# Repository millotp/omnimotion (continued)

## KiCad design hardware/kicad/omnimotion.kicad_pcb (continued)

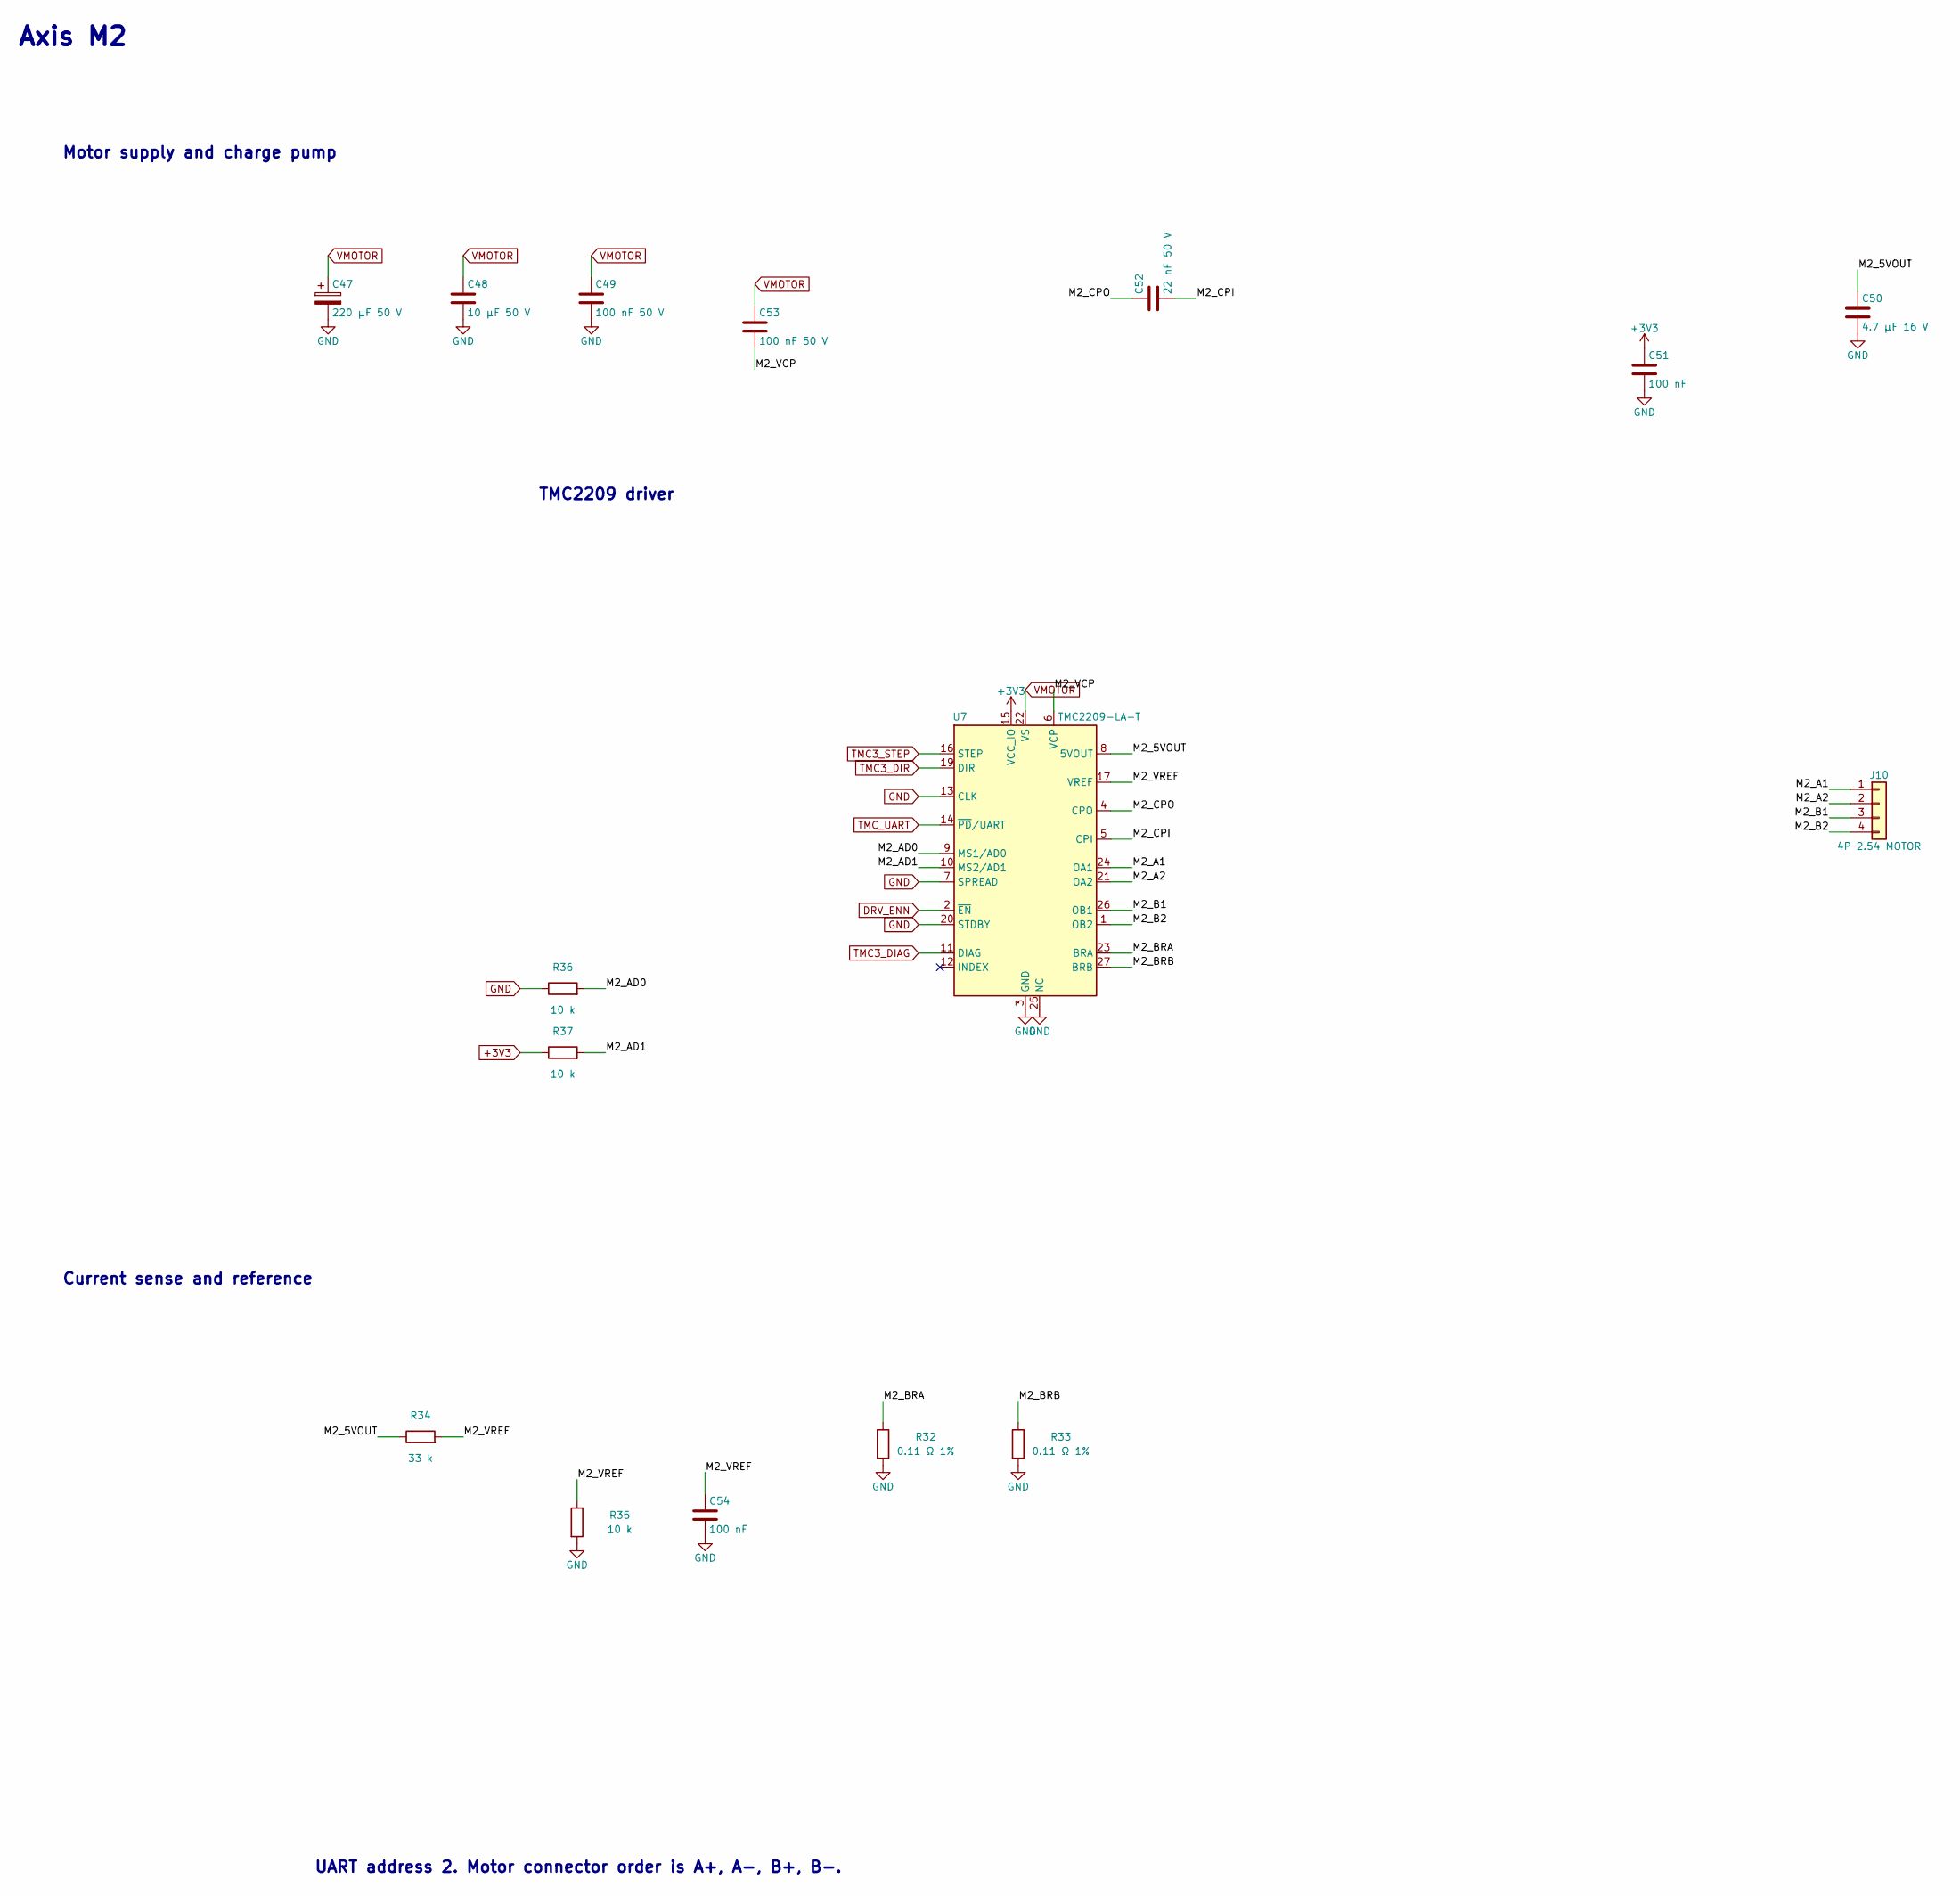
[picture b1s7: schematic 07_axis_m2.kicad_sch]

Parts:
C47: 220 µF 50 V; CP_Elec_10x10.5
C48: 10 µF 50 V; C_1210_3225Metric
C49, C53: 100 nF 50 V; C_0603_1608Metric
C50: 4.7 µF 16 V; C_0603_1608Metric
C51, C54: 100 nF; C_0603_1608Metric
C52: 22 nF 50 V; C_0603_1608Metric
J10: 4P 2.54 MOTOR; PinHeader_1x04_P2.54mm_Vertical
R32, R33: 0.11 Ω 1%; R_2512_6332Metric
R34: 33 k; R_0603_1608Metric
R35, R36, R37: 10 k; R_0603_1608Metric
U7: TMC2209-LA-T; TMC2209_VQFN28_ThermalVias_0.3mm

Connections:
+3V3: C51.1, R37.1, U7.15 (VCC_IO); also elsewhere on the board
/Axis M2 - UART address 2/M2_5VOUT: C50.1, R34.1, U7.8 (5VOUT)
/Axis M2 - UART address 2/M2_A1: J10.1, U7.24 (OA1)
/Axis M2 - UART address 2/M2_A2: J10.2, U7.21 (OA2)
/Axis M2 - UART address 2/M2_AD0: R36.2, U7.9 (MS1/AD0)
/Axis M2 - UART address 2/M2_AD1: R37.2, U7.10 (MS2/AD1)
/Axis M2 - UART address 2/M2_B1: J10.3, U7.26 (OB1)
/Axis M2 - UART address 2/M2_B2: J10.4, U7.1 (OB2)
/Axis M2 - UART address 2/M2_BRA: R32.1, U7.23 (BRA)
/Axis M2 - UART address 2/M2_BRB: R33.1, U7.27 (BRB)
/Axis M2 - UART address 2/M2_CPI: C52.2, U7.5 (CPI)
/Axis M2 - UART address 2/M2_CPO: C52.1, U7.4 (CPO)
/Axis M2 - UART address 2/M2_VCP: C53.2, U7.6 (VCP)
/Axis M2 - UART address 2/M2_VREF: C54.1, R34.2, R35.1, U7.17 (VREF)
DRV_ENN: U7.2 (~EN); also elsewhere on the board
GND: C47.2, C48.2, C49.2, C50.2, C51.2, C54.2, R32.2, R33.2, R35.2, R36.1, U7.3 (GND), U7.7 (SPREAD), U7.13 (CLK), U7.18 (GND), U7.20 (STDBY), U7.25 (NC), U7.29 (GND); also elsewhere on the board
TMC3_DIAG: U7.11 (DIAG); also elsewhere on the board
TMC3_DIR: U7.19 (DIR); also elsewhere on the board
TMC3_STEP: U7.16 (STEP); also elsewhere on the board
TMC_UART: U7.14 (~PD/UART); also elsewhere on the board
VMOTOR: C47.1, C48.1, C49.1, C53.1, U7.22 (VS), U7.28 (VS); also elsewhere on the board

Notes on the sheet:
TMC2209 driver
Motor supply and charge pump
Axis M2
UART address 2. Motor connector order is A+, A−, B+, B−.
Current sense and reference

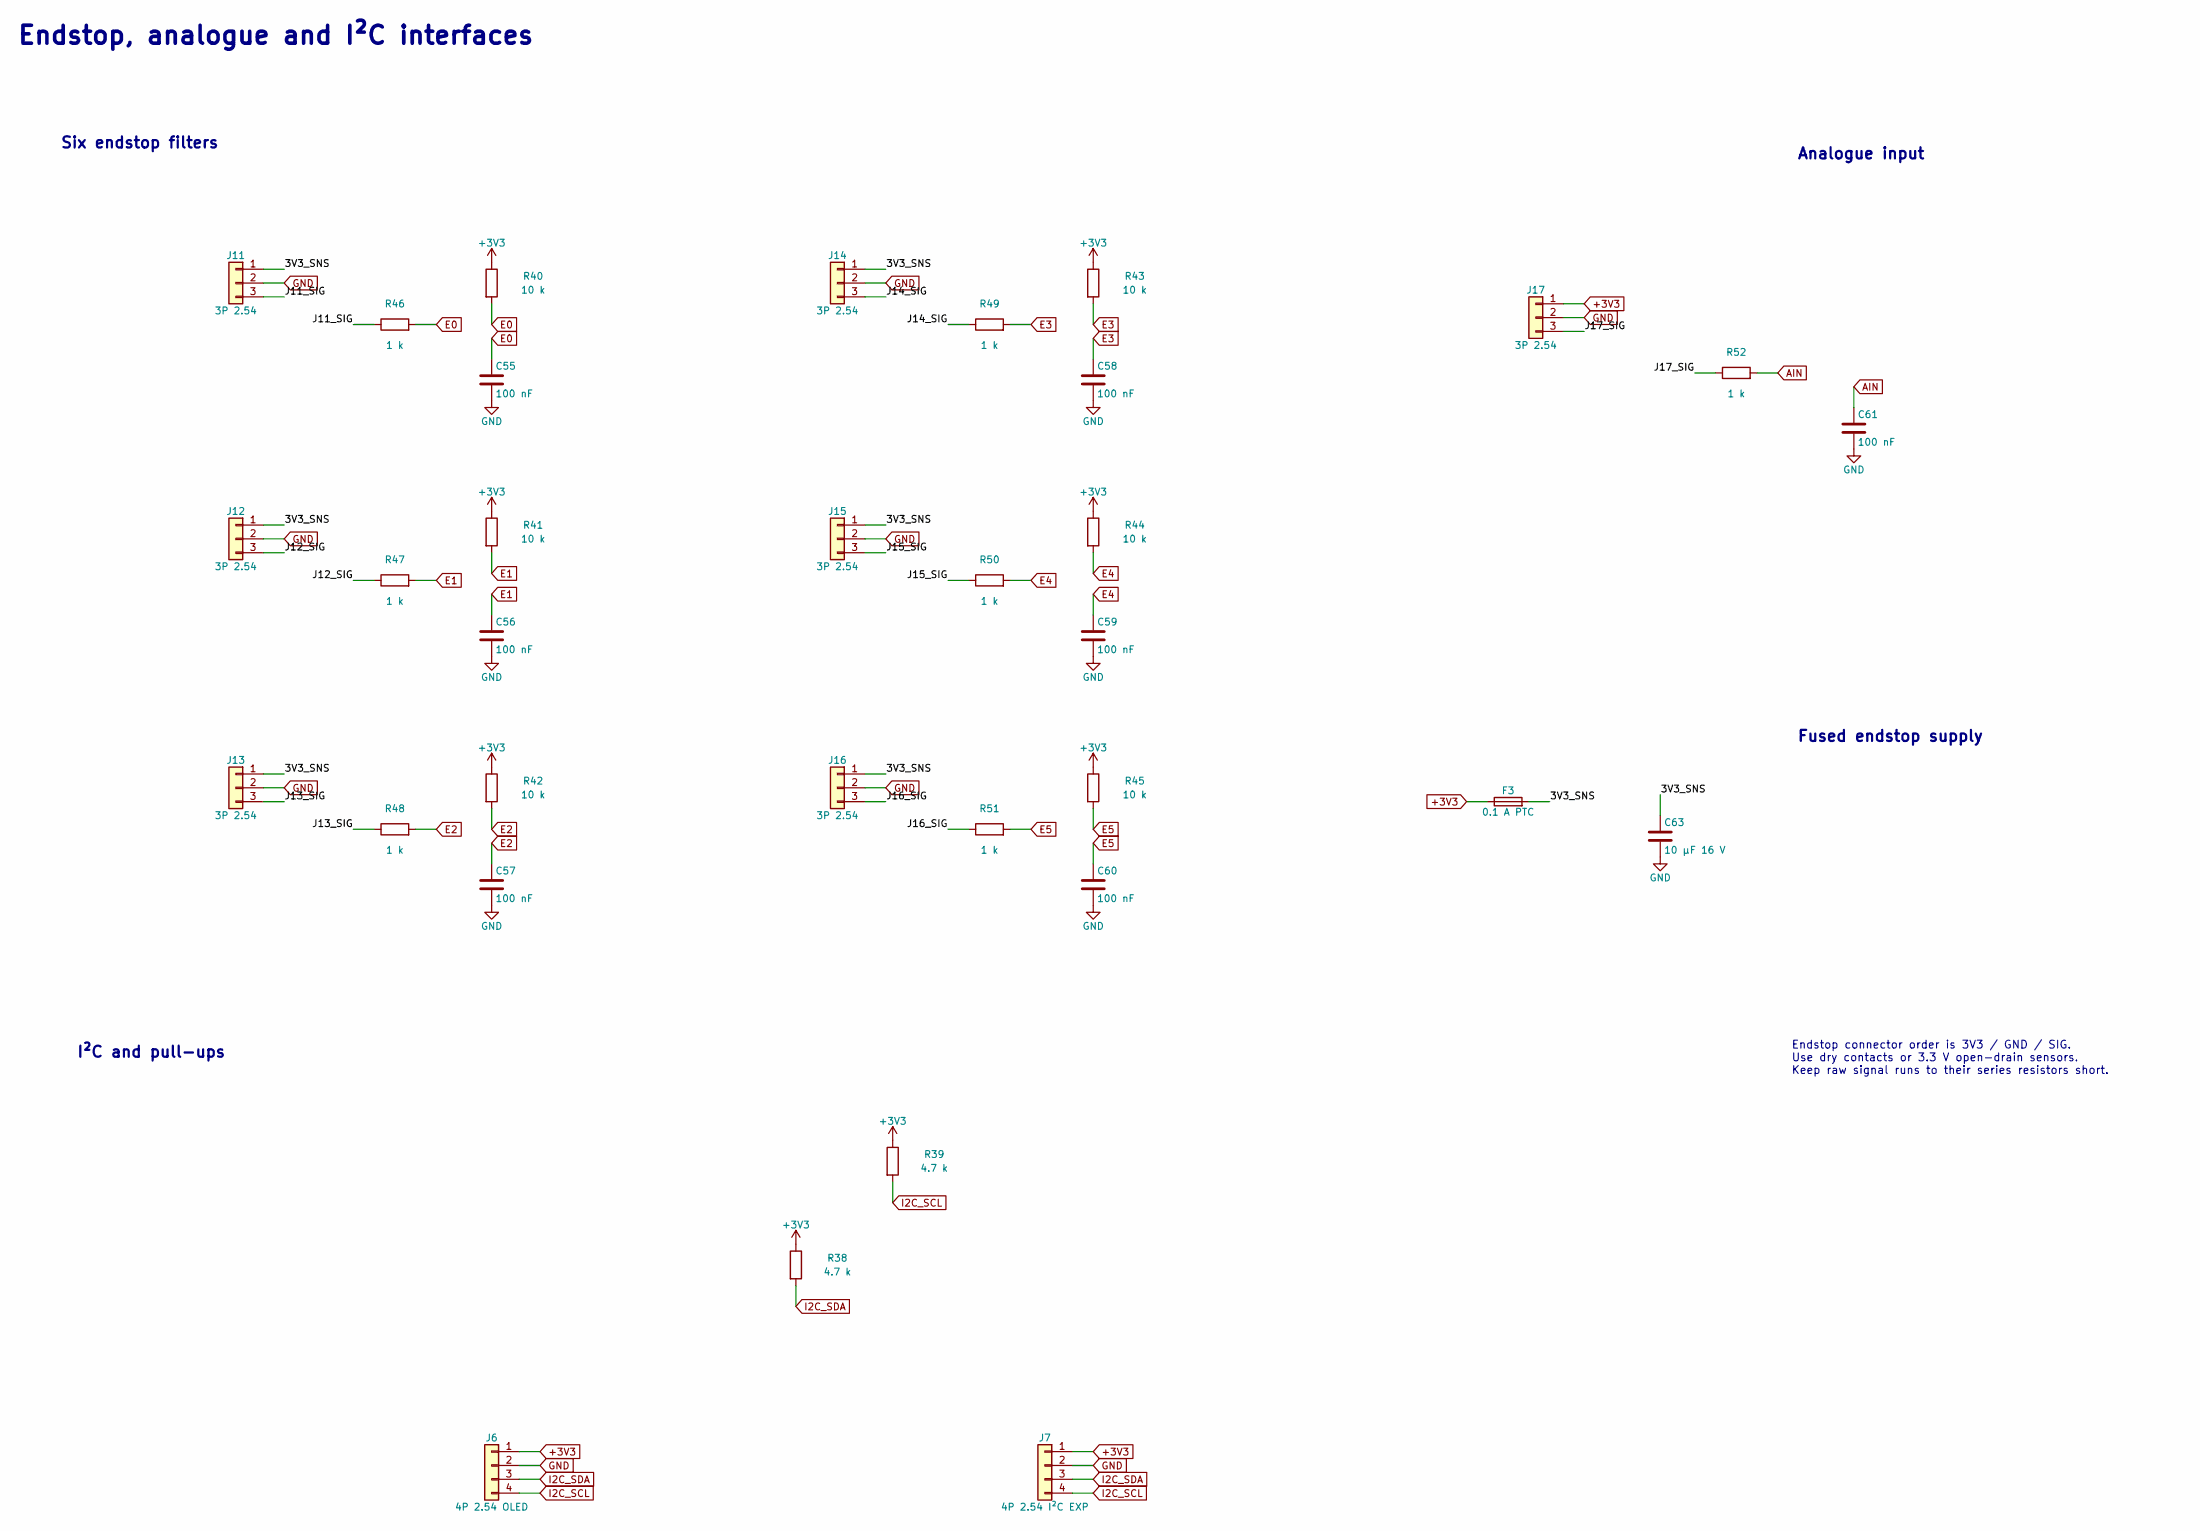
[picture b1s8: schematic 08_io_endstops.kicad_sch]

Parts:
C55, C56, C57, C58, C59, C60, C61: 100 nF; C_0603_1608Metric
C63: 10 µF 16 V; C_0805_2012Metric
F3: 0.1 A PTC; Fuse_1206_3216Metric
J6: 4P 2.54 OLED; PinHeader_1x04_P2.54mm_Vertical
J7: 4P 2.54 I²C EXP; PinHeader_1x04_P2.54mm_Vertical
J11, J12, J13, J14, J15, J16, J17: 3P 2.54; PinHeader_1x03_P2.54mm_Vertical
R38, R39: 4.7 k; R_0603_1608Metric
R40, R41, R42, R43, R44, R45: 10 k; R_0603_1608Metric
R46, R47, R48, R49, R50, R51, R52: 1 k; R_0603_1608Metric

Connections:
+3V3: F3.1, J6.1, J7.1, J17.1, R38.1, R39.1, R40.1, R41.1, R42.1, R43.1, R44.1, R45.1; also elsewhere on the board
/Endstops, analog and I2C/3V3_SNS: C63.1, F3.2, J11.1, J12.1, J13.1, J14.1, J15.1, J16.1
/Endstops, analog and I2C/J11_SIG: J11.3, R46.1
/Endstops, analog and I2C/J12_SIG: J12.3, R47.1
/Endstops, analog and I2C/J13_SIG: J13.3, R48.1
/Endstops, analog and I2C/J14_SIG: J14.3, R49.1
/Endstops, analog and I2C/J15_SIG: J15.3, R50.1
/Endstops, analog and I2C/J16_SIG: J16.3, R51.1
/Endstops, analog and I2C/J17_SIG: J17.3, R52.1
AIN: C61.1, R52.2; also elsewhere on the board
E0: C55.1, R40.2, R46.2; also elsewhere on the board
E1: C56.1, R41.2, R47.2; also elsewhere on the board
E2: C57.1, R42.2, R48.2; also elsewhere on the board
E3: C58.1, R43.2, R49.2; also elsewhere on the board
E4: C59.1, R44.2, R50.2; also elsewhere on the board
E5: C60.1, R45.2, R51.2; also elsewhere on the board
GND: C55.2, C56.2, C57.2, C58.2, C59.2, C60.2, C61.2, C63.2, J6.2, J7.2, J11.2, J12.2, J13.2, J14.2, J15.2, J16.2, J17.2; also elsewhere on the board
I2C_SCL: J6.4, J7.4, R39.2; also elsewhere on the board
I2C_SDA: J6.3, J7.3, R38.2; also elsewhere on the board

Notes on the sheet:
Endstop, analogue and I²C interfaces
Six endstop filters
Analogue input
Fused endstop supply
I²C and pull-ups
Endstop connector order is 3V3 / GND / SIG. Use dry contacts or 3.3 V open-drain sensors. Keep raw signal runs to their series resistors short.

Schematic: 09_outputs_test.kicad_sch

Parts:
C62: 22 µF 16 V; C_1206_3216Metric
D2, D3, D6: SS36; D_SMC
D7: grn VMOTOR; LED_0805_2012Metric
D8: grn 5 V; LED_0805_2012Metric
D9: grn 3V3; LED_0805_2012Metric
J18, J19: 2P 2.54; TerminalBlock_Phoenix_MPT-0,5-2-2.54_1x02_P2.54mm_Horizontal
J20: 3P 2.54 RGB; TerminalBlock_Phoenix_MPT-0,5-3-2.54_1x03_P2.54mm_Horizontal
J21: 4P 2.54 AUX POWER; TerminalBlock_Phoenix_MPT-0,5-4-2.54_1x04_P2.54mm_Horizontal
Q2, Q3: AO3400A; SOT-23
R54, R56, R60: 1 k; R_0603_1608Metric
R55, R57, R59: 10 k; R_0603_1608Metric
R58, R61: 470 R; R_0603_1608Metric
TP3, TP4, TP5, TP6, TP7, TP8, TP9, TP10, TP11, TP12, TP13, TP14: Test point; TestPoint_Pad_D1.0mm

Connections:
5V_SYS: D2.1 (K), D6.2 (A), J18.1, J21.2, R60.1, TP3.1 (1_1); also elsewhere on the board
+3V3: J21.3, R61.1, TP4.1 (1_1); also elsewhere on the board
/Outputs and test points/LED_3V3_A: D9.2 (A), R61.2
/Outputs and test points/LED_5V_A: D8.2 (A), R60.2
/Outputs and test points/LED_VM_A: D7.2 (A), R59.2
/Outputs and test points/OUT1_GATE: Q2.1 (G), R54.2, R55.1
/Outputs and test points/OUT1_SW: D2.2 (A), J18.2, Q2.3 (D)
/Outputs and test points/OUT2_GATE: Q3.1 (G), R56.2, R57.1
/Outputs and test points/OUT2_SW: D3.2 (A), J19.2, Q3.3 (D)
/Outputs and test points/RGB_5V: C62.1, D6.1 (K), J20.1
/Outputs and test points/RGB_DIN: J20.2, R58.2
ESTOP_SENSE: TP13.1 (1_1); also elsewhere on the board
GND: C62.2, D7.1 (K), D8.1 (K), D9.1 (K), J20.3, J21.4, Q2.2 (S), Q3.2 (S), R55.2, R57.2, TP5.1 (1_1), TP6.1 (1_1); also elsewhere on the board
I2C_SCL: TP12.1 (1_1); also elsewhere on the board
I2C_SDA: TP11.1 (1_1); also elsewhere on the board
OUT1_EN: R54.1; also elsewhere on the board
OUT2_EN: R56.1; also elsewhere on the board
RGB_DATA: R58.1; also elsewhere on the board
TMC1_STEP: TP14.1 (1_1); also elsewhere on the board
TMC_UART: TP10.1 (1_1); also elsewhere on the board
TMC_UART_TX: TP9.1 (1_1); also elsewhere on the board
USB_D+: TP7.1 (1_1); also elsewhere on the board
USB_D-: TP8.1 (1_1); also elsewhere on the board
VMOTOR: D3.1 (K), J19.1, J21.1, R59.1; also elsewhere on the board

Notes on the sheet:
Switched outputs, RGB, auxiliary power and test points
OUT1 • 5 V low side
OUT2 • VMOTOR low side
3.3 V-compatible RGB data
Rail indicators
Auxiliary power
Bench test points
Fit D2 and D3 for inductive loads. OUT2 remains powered when the driver stop opens. Probe TP1 through TP4 to check the power rails. TP5 and TP6 provide probe grounds.

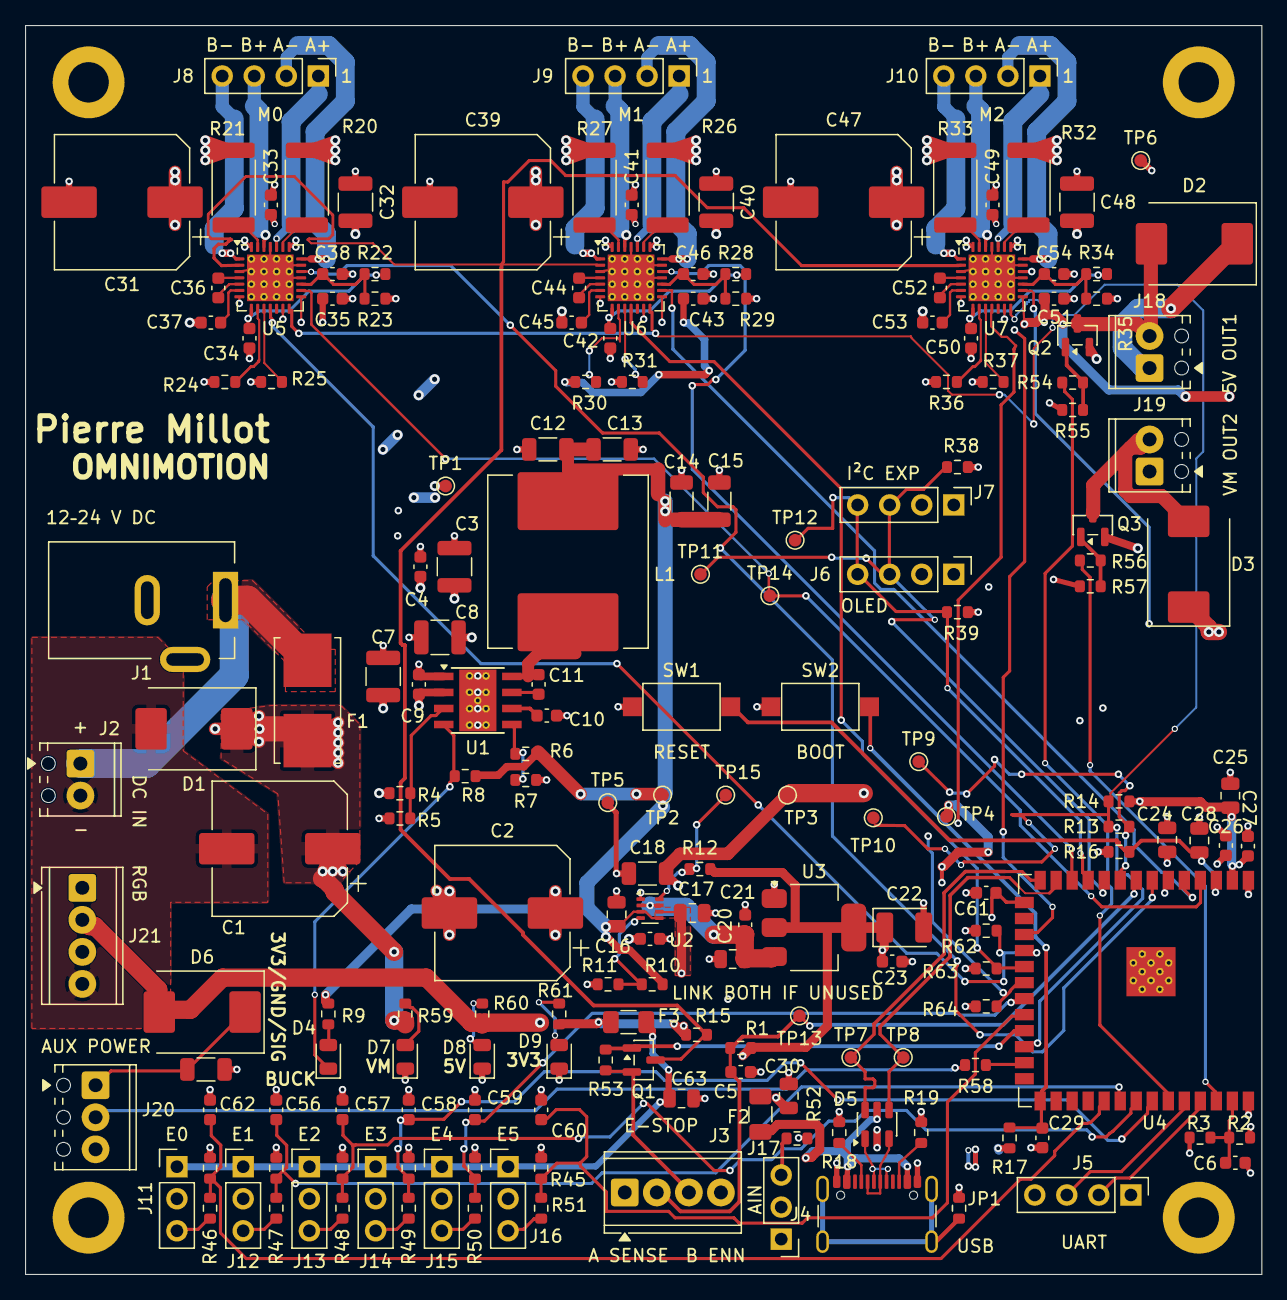
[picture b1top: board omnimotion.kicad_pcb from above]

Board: 4 copper layers, 98.0 x 99.0 mm, 193 parts (0 on the bottom side), 112 nets.

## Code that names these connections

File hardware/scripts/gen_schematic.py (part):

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            "   the driver through ENN, which is what every RAMPS-class board",
            "   does. D1 alone handles surge and reverse polarity - it opens",
            "   F1 - so feed this board 12-24 V and nothing else.",
            "2. J3 is a 2-pole NC e-stop. Pole A drives ESTOP_SENSE (GPIO15) "
            "so",
            "   firmware can stop the planner; pole B sits in series with "
            "Q1's",
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            "   the button is closed. That part is copper, not firmware.",
            "3. Six endstops land on GPIO38-41 + GPIO13/14, straight onto the",
            "   MCU with no I\u00b2C expander anywhere in the path.",
            "4. One analogue input: J17 \u2192 GPIO3 (ADC1_CH2). VMOTOR is",
            "   monitored on GPIO1 (ADC1_CH0) by the on-chip 12-bit ADC.",
            "5. Three axes (U5-U7, J8-J10) and two outputs: discrete AO3400A",
            "   low-side switches, OUT1 5 V on J18, OUT2 24 V on J19.",
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    s.arrow((1060, Y), (1060, 128))
    s.text(1070, 118, "to 3\u00d7 TMC2209 VS (sheets 5-7)", "ts")
    s.text(1070, 131, "and the 24 V output (sheet 9)", "ts")
    s.netlabel(1210, Y, "VMOTOR", "r", "flagp")

    # -------------------------------------------------------- VMOTOR monitor
    s.zone(56, 540, 620, 260, "VMOTOR MONITOR \u2192 GPIO1 / ADC1_CH0")
    s.netlabel(200, 610, "VMOTOR", "l", "flagp")
    s.line(200, 610, 230, 610)
    s.res_h(230, 610, "R2", "100 k", 100)
    s.line(330, 610, 390, 610)
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    s.dot(480, 610)
    s.gnd(480, c10["2"][1])
    s.line(480, 610, 570, 610)
    s.netlabel(570, 610, "VMON", "r", "flagp")
    s.text(90, 750, "24 V \u2192 2.18 V and 30 V \u2192 2.73 V, both inside "
                    "the ESP32-S3 ADC1 range at", "ts")
    s.text(90, 766, "11 dB attenuation. Firmware only needs \"is bulk "
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    c5 = s.cap_v(510, sense, "C5", "100 nF")
    s.dot(510, sense)
    s.gnd(510, c5["2"][1])
    s.netlabel(640, sense, "ESTOP_SENSE", "r")
    s.text(300, 1195, "closed \u2192 low = running   \u00b7   pressed or "
                      "cable cut \u2192 high = stopped", "ts")

    # pole B: sits in the TMC2209 ENN pull-down return
    s.line(*j3["B1"], 300, j3["B1"][1])
    s.netlabel(300, j3["B1"][1], "ENN_RTN", "r")
    s.line(*j3["B2"], 270, j3["B2"][1])
    s.gnd(270, j3["B2"][1])

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    # ============================================================ LMR33630
    s.zone(46, 92, 1750, 540, "5 V / 3 A STEP-DOWN \u2014 TI recommended "
                              "configuration for 400 kHz, V_OUT = 5 V")
    s.netlabel(180, 210, "VMOTOR", "l", "flagp")
    s.line(180, 210, 540, 210)
    s.text(200, 168, "Tapped straight off VMOTOR, downstream of F1 and D1 on "
                     "sheet 2. There is no separate buck fuse or TVS.", "ts")
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            "ST is open-drain and pulls LOW while VIN1 is NOT in use, i.e. "
            "\"running on USB\". TP15 exposes it; it is deliberately not",
            "wired to a GPIO because the only spare pins are GPIO45/46, "
            "which are strapping pins - read VMON instead.",
            "The mux is rated 2.5 A, below the buck's 3 A. Loads above ~2 A "
            "(big LED strips) must be fed from their own connector,",
            "not through 5V_SYS."])
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    s.res_v(200, 400, "R16", "10 k")
    s.line(200, 464, 200, 490)
    s.dot(200, 490)
    s.netlabel(140, 490, "EN_MCU", "l")
    s.line(140, 490, 200, 490)
    c34 = s.cap_v(300, 510, "C28", "10 \u00b5F", 52)
    s.wire((200, 490), (300, 490), (300, 510))
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    s.res_v(200, 810, "R17", "10 k")
    s.line(200, 874, 200, 900)
    s.dot(200, 900)
    s.netlabel(140, 900, "IO0_BOOT", "l")
    s.line(140, 900, 200, 900)
    c35 = s.cap_v(300, 920, "C29", "100 nF", 52)
    s.wire((200, 900), (300, 900), (300, 920))
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                ["3V3", "U0TXD", "U0RXD", "GND"], 120, "right", 32)
    s.rail(1330, 917, "+3V3")
    s.line(1290, 917, 1330, 917)
    s.netlabel(1400, 949, "U0TXD", "r")
    s.line(1290, 949, 1400, 949)
    s.netlabel(1400, 981, "U0RXD", "r")
    s.line(1290, 981, 1400, 981)
    s.wire(j5["GND"], (1340, 1013), (1340, 1038))
    s.gnd(1340, 1038)
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            "3V3 (sheet 8), each output gate a",
            "  10 k pull-down (sheet 9) and each DIAG input a 100 k pull-down "
            "(sheet 5), so nothing is left to the pin's own reset behaviour. "
            "DRV_EN on GPIO21 is the exception \u2014 see sheet 5.",
            "\u2022 ANTENNA: the module must overhang the PCB edge. Keepout of "
            "\u2265 15 mm with no copper, no traces and no ground on any of the "
            "four layers, and no metal (motors,",
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    s.wire(u["VS"], (530, 170))
    s.line(150, 170, 530, 170)
    s.dot(460, 170)
    s.netlabel(150, 170, "VMOTOR", "l", "flagp")
    for x, cref, val, pol in ((200, C[0], "220 \u00b5F 50 V", True),
                              (280, C[1], "10 \u00b5F 50 V", False),
                              (360, C[2], "100 nF 50 V", False)):
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    # ==================================================== shared: UART bus
    s.zone(1330, 90, 466, 340, "SINGLE-WIRE UART BUS \u2014 shared by U5-U7 "
                               "(datasheet fig. 4.1)")
    s.netlabel(1450, 200, "TMC_UART_TX", "l")
    s.line(1450, 200, 1490, 200)
    s.res_h(1490, 200, "R13", "1 k", 80)
    s.wire((1570, 200), (1620, 200), (1620, 270))
    s.line(1450, 270, 1700, 270)
    s.netlabel(1450, 270, "TMC_UART", "l")
    s.dot(1620, 270)
    s.rail(1700, 180, "+3V3")
    s.res_v(1700, 180, "R14", "10 k")
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    s.line(1506, 574, 1506, 640)
    s.dot(1506, 590)
    s.line(1506, 590, 1600, 590)
    s.netlabel(1600, 590, "DRV_ENN", "r")
    s.mosfet(1440, 640, "Q1", "AO3400A")
    s.netlabel(1380, 674, "DRV_EN", "l")
    s.line(1380, 674, 1440, 674)
    s.dot(1380, 674)
    r53 = s.res_v(1380, 674, "R53", "10 k", 74, side="l")
    s.line(1380, r53["2"][1], 1506, 748)
    s.line(1506, 708, 1506, 748)
    s.netlabel(1506, 748, "ENN_RTN", "r")
    s.text(1340, 790, "Q1's source is ENN_RTN, not GND: e-stop pole B on J3 "
                      "(sheet 2) closes", "ts")
    s.text(1340, 804, "that return in copper. ENN can therefore only be "
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    s.line(1170, 259, 1170, 275)
    s.gnd(1170, c61["2"][1])
    s.line(1170, 259, 1210, 259)
    s.netlabel(1210, 259, "AIN", "r")
    s.text(866, 384, "The board has one analogue input. GPIO3 is ADC1_CH2, "
                     "so it", "ts")
    s.text(866, 400, "can be read while WiFi is up \u2014 ADC2 cannot. "
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             ["E3      J14", "GPIO41"],
             ["E4      J15", "GPIO13"],
             ["E5      J16", "GPIO14"],
             ["AIN     J17", "GPIO3 / ADC1_CH2"],
             ["I2C_SDA J6/J7", "GPIO17"],
             ["I2C_SCL J6/J7", "GPIO18"]],
            [250, 200], "WHAT THIS SHEET COSTS IN GPIO")

    s.note(1346, 340, 450, "WHY ENDSTOPS GO STRAIGHT TO THE MCU",
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            "plus GPIO13/14 carry them, and the table above is the bill.",
            "",
            "The same argument covers the analogue side. One input on GPIO3",
            "(ADC1_CH2) and VMOTOR sensing on GPIO1 (ADC1_CH0) both use the",
            "on-chip 12-bit ADC, so there is no external ADC and nothing on",
            "the I\u00b2C bus that the board itself depends on."])

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    s.line(500, 820, 500, 896)
    s.res_v(500, 896, "R38", "4.7 k")
    s.line(140, 880, 790, 880)
    s.netlabel(140, 880, "I2C_SCL", "l")
    s.line(140, 960, 750, 960)
    s.netlabel(140, 960, "I2C_SDA", "l")
    s.dots((500, 960), (560, 880))

    j6 = s.conn(180, 1010, "J6", "4P 2.54  OLED", ["3V3", "GND", "SDA", "SCL"],
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    s.gnd(1000, c81["2"][1])
    s.wire((1120, 160), (1120, 229), (1160, 229))

    s.netlabel(760, 300, "RGB_DATA", "l")
    s.line(760, 300, 1000, 300)
    s.res_h(1000, 300, "R58", "470 R", 64)
    s.wire((1064, 300), (1140, 300), (1140, 269), (1160, 269))
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    s.zone(1326, 84, 470, 260, "AUX POWER TAKE-OFF")
    j26 = s.conn(1380, 140, "J21", "4P 2.54  AUX POWER",
                 ["VMOTOR", "5V_SYS", "3V3", "GND"], 160, "right", 30)
    for pin, net in (("VMOTOR", "VMOTOR"), ("5V_SYS", "5V_SYS"),
                     ("3V3", "+3V3")):
        p = j26[pin]
        s.netlabel(p[0], p[1], net, "r", "flagp")
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            "   must pull LOW, which is the mux reporting it has handed over.",
            "4. Fit U4. Confirm USB enumeration and flash a blink sketch. "
            "GPIO0 strap",
            "   check. Read VMON on GPIO1 and confirm it tracks the input.",
            "5. Close J3 (or link A1-A2 and B1-B2). Confirm ESTOP_SENSE goes "
            "low.",
            "6. Fit Q1. With the ESP32 held in reset, confirm DRV_ENN sits at "
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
